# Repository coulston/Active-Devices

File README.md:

Here is a set of resources that I've developed while a faculty member at the Colorado School of Mines.  These resources come in two flavors:

## Laboratories

The labs presented here require students to predict circuit behavior using circuit theory, simulate the circuit, and then build the circuit.  The first two
sets of labs below require multiple lab session to complete, showing students how combine building block circuits to produce complex behavior.
* The design/test/assembly of a BJT curve tracer on a custom PCB.  Based on w2aew's design presented on this [YouTube](https://www.youtube.com/watch?v=ZOLLoa2fH24) video.
* The design/test/assembly of an audio amplifier and audio frequency filters on a custom PCB.
* The analysis of a prebuilt, fully analog, PID controller.
* The analysis of a prebuilt full-bridge Rectifier/Buck converter.

## Workbook
I remember working problems from Schaums outline series as an undergraduate.  Working a long series of similar but distinct circuit
problems helped me hone my skill.  Most textbooks have a small set of problems to work; a volume that did not consistently produce
mastery in my students.  So I spent a summer writing the circuit problems that you will find here.  This is a work in progress and
I would certianly apprecaite any suggestions for problems to add.

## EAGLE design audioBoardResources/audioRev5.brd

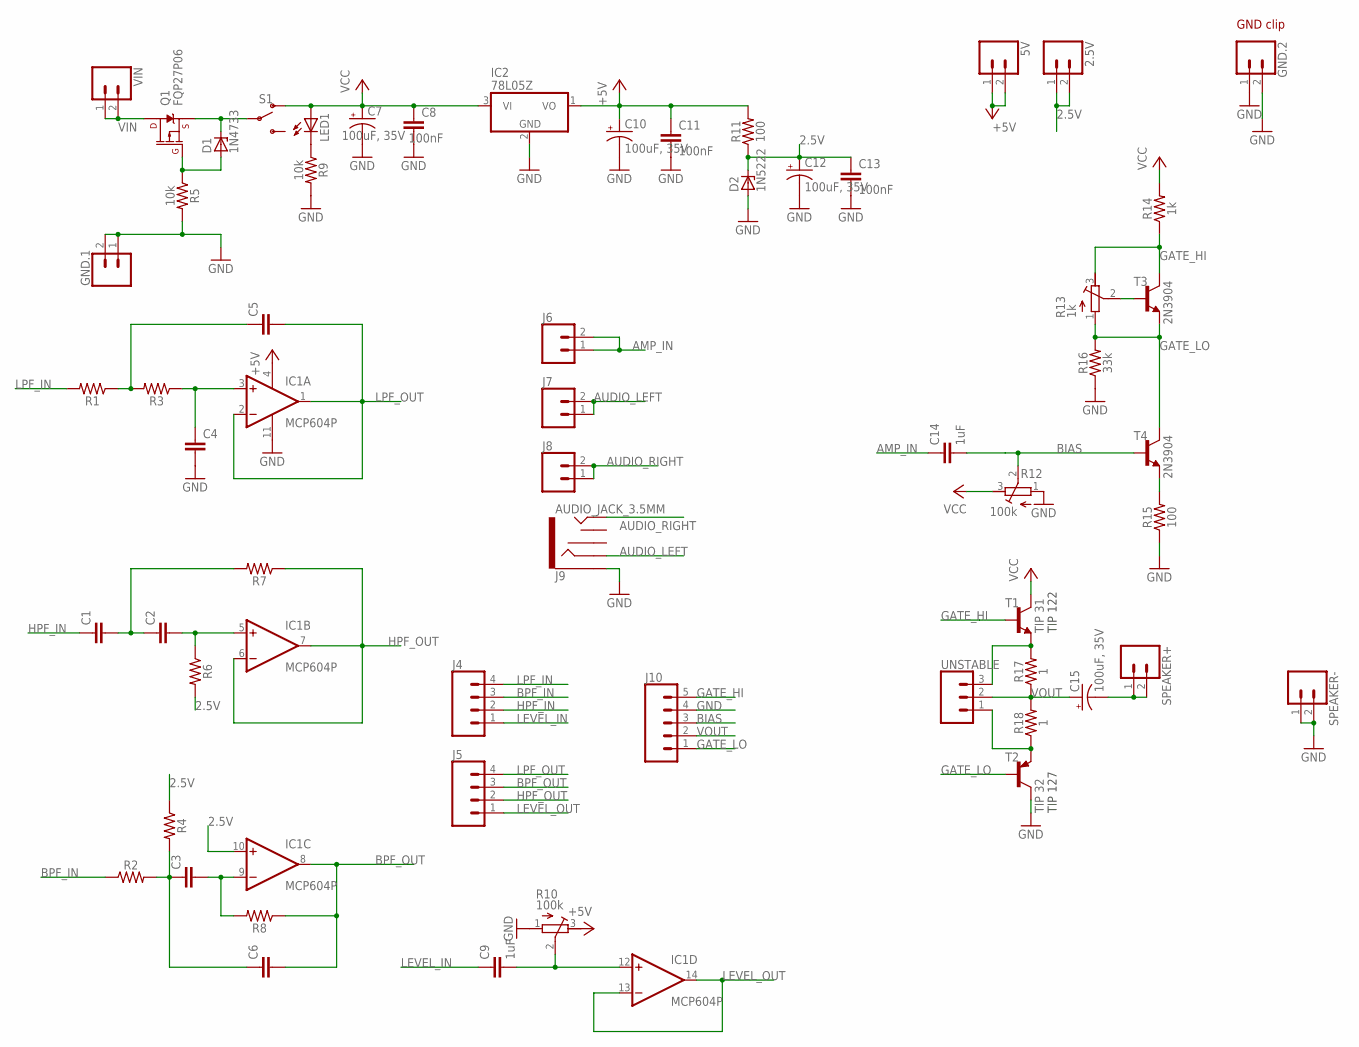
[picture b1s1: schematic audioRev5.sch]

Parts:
2.5V, 5V: CONN_02; 1X02
C1, C2, C3, C4, C5, C6: C-EU025-025X050; C025-025X050
C7, C10, C12, C15: 100uF, 35V; E2,5-6
C8, C11, C13: 100nF; C025-025X050
C9, C14: 1uF; C025-025X050
D1: 1N4733; DO41Z10
D2: 1N5222; DO34Z7
GND.1, GND.2: CONN_02; 1X02
IC1: MCP604P; DIL14
IC2: 78L05Z; TO92
J4, J5: CONN_04LOCK_LONGPADS; 1X04_LOCK_LONGPADS
J6, J7, J8: CONN_02; 1X02
J9: AUDIO_JACK_3.5MM; AUDIO-JACK
J10: CONN_05PTH_LONGPADS; 1X05_LONGPADS
LED1: LED5MM
Q1: FQP27P06; TO220V
R1, R2, R3, R4, R6, R7, R8: RESISTORAXIAL-0.3; AXIAL-0.3
R5, R9: 10k; AXIAL-0.3
R10, R12: 100k; RTRIM3296W
R11, R15: 100; AXIAL-0.3
R13: 1k; RTRIM3296W
R14: 1k; AXIAL-0.3
R16: 33k; AXIAL-0.3
R17, R18: 1; AXIAL-0.3
S1: SWITCH-SPDT-PTH-11.6X4.0MM; SWITCH_SPDT_PTH_11.6X4.0MM
SPEAKER+: CONN_02; 1X02
SPEAKER-: CONN_02; 1X02
T1: TIP 31; TO220V
T2: TIP 32; TO220V
T3, T4: 2N3904; TO92-EBC
UNSTABLE: CONN_03LOCK_LONGPADS; 1X03_LOCK_LONGPADS
VIN: CONN_02; 1X02

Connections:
2.5V: 2.5V.1, 2.5V.2, C12.+, C13.1, D2.C, IC1.10 (+IN), R4.P$1 (1), R6.P$2 (2), R11.P$1 (1)
+5V: 5V.1, 5V.2, C10.+, C11.1, IC1.4 (V+), IC2.1 (VO), R10.3 (E), R11.P$2 (2)
AMP_IN: C14.1, J6.1, J6.2
AUDIO_LEFT: J7.1, J7.2, J9.RING
AUDIO_RIGHT: J8.1, J8.2, J9.TIP
BIAS: C14.2, J10.3, R12.2 (S), T4.B
BPF_IN: J4.3, R2.P$1 (1)
BPF_OUT: C6.2, IC1.8 (OUT), J5.3, R8.P$1 (1)
GATE: D1.A, Q1.1 (G), R5.P$1 (1)
GATE_HI: J10.5, R13.3 (E), R14.P$1 (1), T1.1 (B), T3.C
GATE_LO: J10.1, R13.1 (A), R16.P$2 (2), T2.1 (B), T3.E, T4.C
GND: C4.2, C7.-, C8.2, C10.-, C11.2, C12.-, C13.2, D2.A, GND.1.1, GND.1.2, GND.2.1, GND.2.2, IC1.11 (V-), IC2.2 (GND), J9.SLEEVE, J10.4, R5.P$2 (2), R9.P$2 (2), R10.1 (A), R12.1 (A), R15.P$1 (1), R16.P$1 (1), SPEAKER-.1, SPEAKER-.2, T2.2 (C)
HPF_IN: C1.1, J4.2
HPF_OUT: IC1.6 (-IN), IC1.7 (OUT), J5.2, R7.P$1 (1)
LEVEL_IN: C9.1, J4.1
LEVEL_OUT: IC1.13 (-IN), IC1.14 (OUT), J5.1
LPF_IN: J4.4, R1.P$2 (2)
LPF_OUT: C5.2, IC1.1 (OUT), IC1.2 (-IN), J5.4
unnamed: R18.P$1 (1), T2.3 (E), UNSTABLE.1
unnamed: R17.P$2 (2), T1.3 (E), UNSTABLE.3
unnamed: R15.P$2 (2), T4.E
unnamed: C3.1, C6.1, R2.P$2 (2), R4.P$2 (2)
unnamed: C4.1, IC1.3 (+IN), R3.P$1 (1)
unnamed: C5.1, R1.P$1 (1), R3.P$2 (2)
unnamed: C3.2, IC1.9 (-IN), R8.P$2 (2)
unnamed: C2.2, IC1.5 (+IN), R6.P$1 (1)
unnamed: C1.2, C2.1, R7.P$2 (2)
unnamed: C9.2, IC1.12 (+IN), R10.2 (S)
unnamed: C15.-, SPEAKER+.1, SPEAKER+.2
unnamed: LED1.K (C), R9.P$1 (1)
unnamed: R13.2 (S), T3.B
SOURCE: D1.C, Q1.3 (S), S1.2
VCC: C7.+, C8.1, IC2.3 (VI), LED1.A, R12.3 (E), R14.P$2 (2), S1.1 (O), T1.2 (C)
VIN: Q1.2 (D), VIN.1, VIN.2
VOUT: C15.+, J10.2, R17.P$1 (1), R18.P$2 (2), UNSTABLE.2

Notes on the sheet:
GND clip
TIP 122
TIP 127

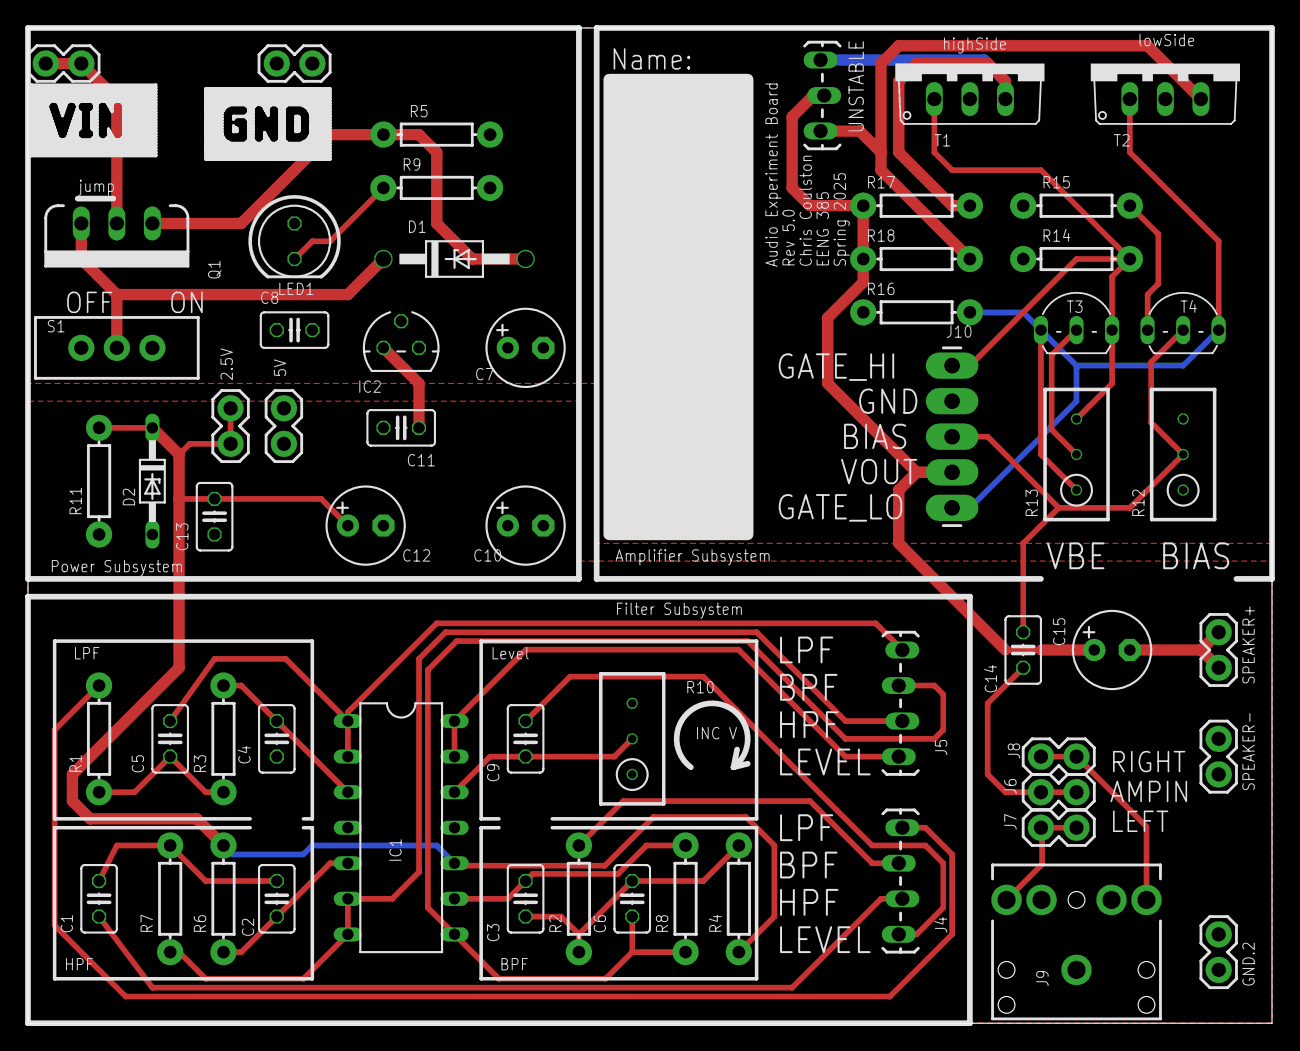
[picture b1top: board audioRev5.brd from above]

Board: 2 copper layers, 88.9 x 71.1 mm, 59 parts (0 on the bottom side), 35 nets.

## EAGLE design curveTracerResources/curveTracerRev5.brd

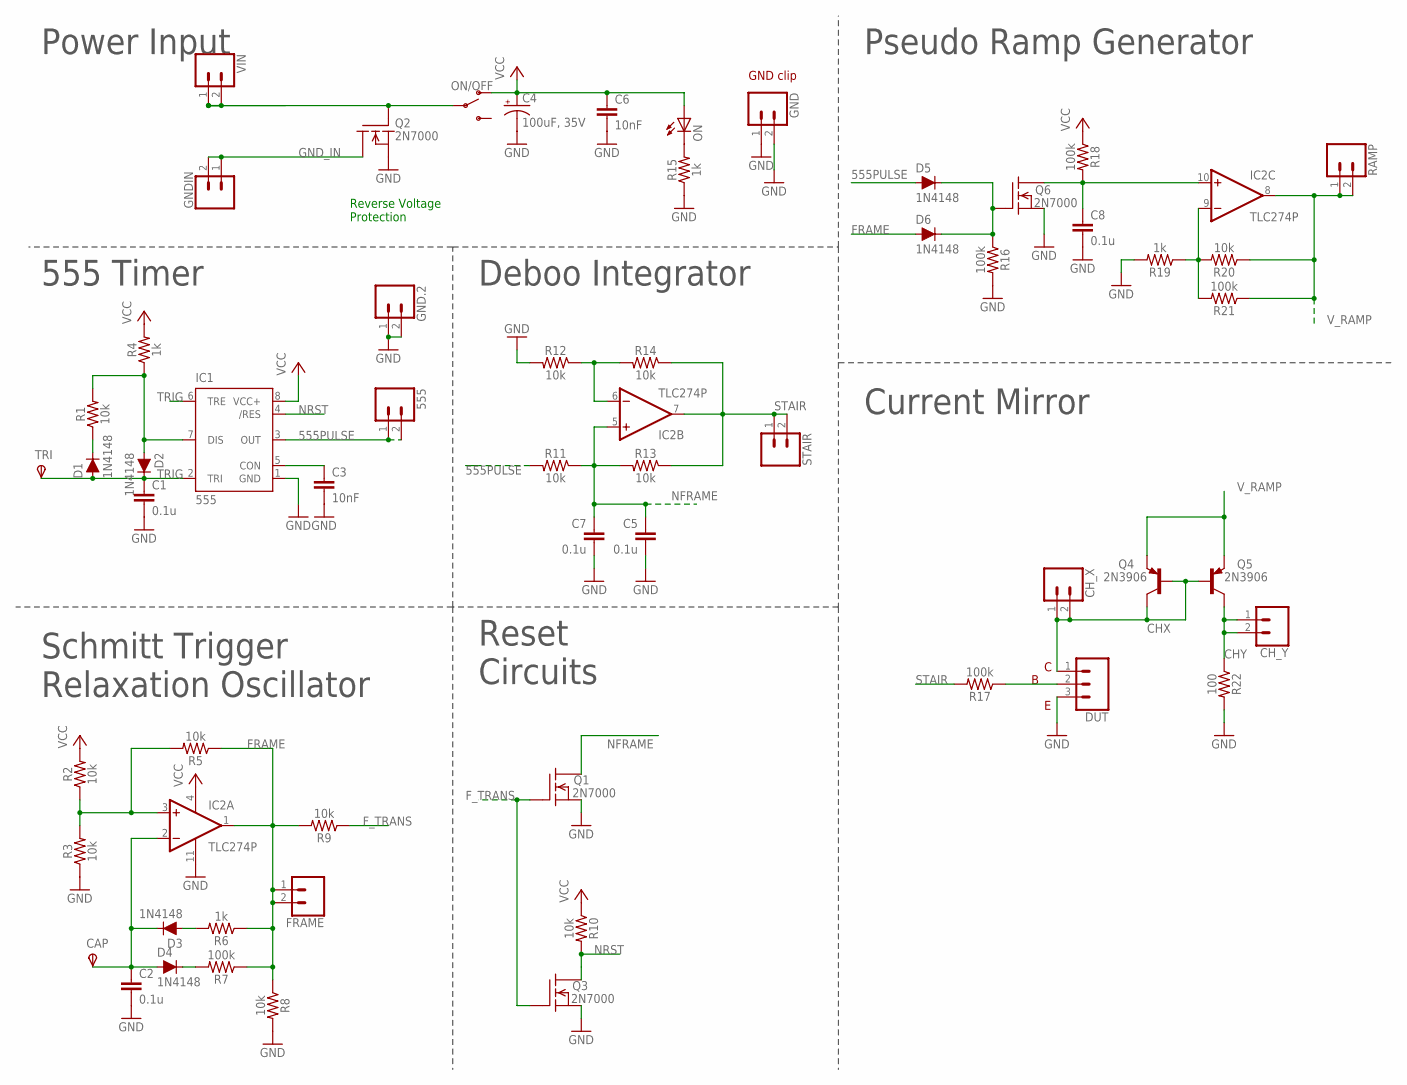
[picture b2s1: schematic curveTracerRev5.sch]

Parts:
555: CONN_02; 1X02
C1, C2, C5, C7, C8: 0.1u; C050-024X044
C3, C6: 10nF; C050-024X044
C4: 100uF, 35V; E2,5-6
CAP: TPSPAD1-13Y; P1-13Y
CH_X: CONN_02; 1X02
CH_Y: CONN_02; 1X02
D1, D2, D3, D4, D5, D6: 1N4148; DIODE-1N4148
DUT: CONN_03LOCK_LONGPADS; 1X03_LOCK_LONGPADS
FRAME: CONN_02; 1X02
GND, GND.2: CONN_02; 1X02
GNDIN: CONN_02; 1X02
IC1: 555; DIP08
IC2: TLC274P; DIL14
ON: LED5MM
ON/OFF: SWITCH-SPDT-PTH-11.6X4.0MM; SWITCH_SPDT_PTH_11.6X4.0MM
Q1, Q2, Q3, Q6: 2N7000; TO-92
Q4, Q5: 2N3906; TO92
R1, R2, R3, R5, R8, R9, R10, R11, R12, R13, R14, R20: 10k; AXIAL-0.3
R4, R6, R15, R19: 1k; AXIAL-0.3
R7, R16, R17, R18, R21: 100k; AXIAL-0.3
R22: 100; AXIAL-0.3
RAMP: CONN_02; 1X02
STAIR: CONN_02; 1X02
TRI: TPSPAD1-13Y; P1-13Y
VIN: CONN_02; 1X02

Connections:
555PULSE: 555.1, 555.2, D5.A, IC1.3 (OUT), R11.P$2 (2)
CHX: CH_X.1, CH_X.2, DUT.1, Q4.1 (C), Q4.2 (B), Q5.2 (B)
CHY: CH_Y.1, CH_Y.2, Q5.1 (C), R22.P$1 (1)
FRAME: D6.A, FRAME.1, FRAME.2, IC2.1 (OUT), R5.P$1 (1), R6.P$1 (1), R7.P$1 (1), R8.P$1 (1), R9.P$2 (2)
F_TRANS: Q1.2 (G), Q3.2 (G), R9.P$1 (1)
GND: C1.2, C2.2, C3.2, C4.-, C5.2, C6.2, C7.2, C8.2, DUT.3, GND.1, GND.2, GND.2.1, GND.2.2, IC1.1 (GND), IC2.11 (V-), Q1.1 (S), Q2.1 (S), Q3.1 (S), Q6.1 (S), R3.P$1 (1), R8.P$2 (2), R12.P$2 (2), R15.P$1 (1), R16.P$2 (2), R19.P$2 (2), R22.P$2 (2)
GND_IN: GNDIN.1, GNDIN.2, Q2.3 (D)
unnamed: ON/OFF.2, Q2.2 (G), VIN.1, VIN.2
unnamed: ON.K (C), R15.P$2 (2)
unnamed: D1.C, R1.P$1 (1)
unnamed: D2.A, IC1.7 (DIS), R1.P$2 (2), R4.P$1 (1)
unnamed: D3.A, R6.P$2 (2)
unnamed: C3.1, IC1.5 (CON)
unnamed: C2.1, CAP.TP, D3.C, D4.A, IC2.2 (-IN)
unnamed: IC2.3 (+IN), R2.P$1 (1), R3.P$2 (2), R5.P$2 (2)
unnamed: D4.C, R7.P$2 (2)
unnamed: D5.C, D6.C, Q6.2 (G), R16.P$1 (1)
unnamed: DUT.2, R17.P$1 (1)
unnamed: IC2.6 (-IN), R12.P$1 (1), R14.P$2 (2)
unnamed: IC2.9 (-IN), R19.P$1 (1), R20.P$2 (2), R21.P$2 (2)
unnamed: C8.1, IC2.10 (+IN), Q6.3 (D), R18.P$2 (2)
NFRAME: C5.1, C7.1, IC2.5 (+IN), Q1.3 (D), R11.P$1 (1), R13.P$2 (2)
NRST: IC1.4 (/RES), Q3.3 (D), R10.P$2 (2)
STAIR: IC2.7 (OUT), R13.P$1 (1), R14.P$1 (1), R17.P$2 (2), STAIR.1, STAIR.2
TRIG: C1.1, D1.A, D2.C, IC1.2 (TRI), IC1.6 (TRE), TRI.TP
VCC: C4.+, C6.1, IC1.8 (VCC+), IC2.4 (V+), ON.A, ON/OFF.1 (O), R2.P$2 (2), R4.P$2 (2), R10.P$1 (1), R18.P$1 (1)
V_RAMP: IC2.8 (OUT), Q4.3 (E), Q5.3 (E), R20.P$1 (1), R21.P$1 (1), RAMP.1, RAMP.2

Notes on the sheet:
GND clip
Power Input
555 Timer
Schmitt Trigger Relaxation Oscillator
Deboo Integrator
Reset Circuits
Pseudo Ramp Generator
Current Mirror
Reverse Voltage Protection

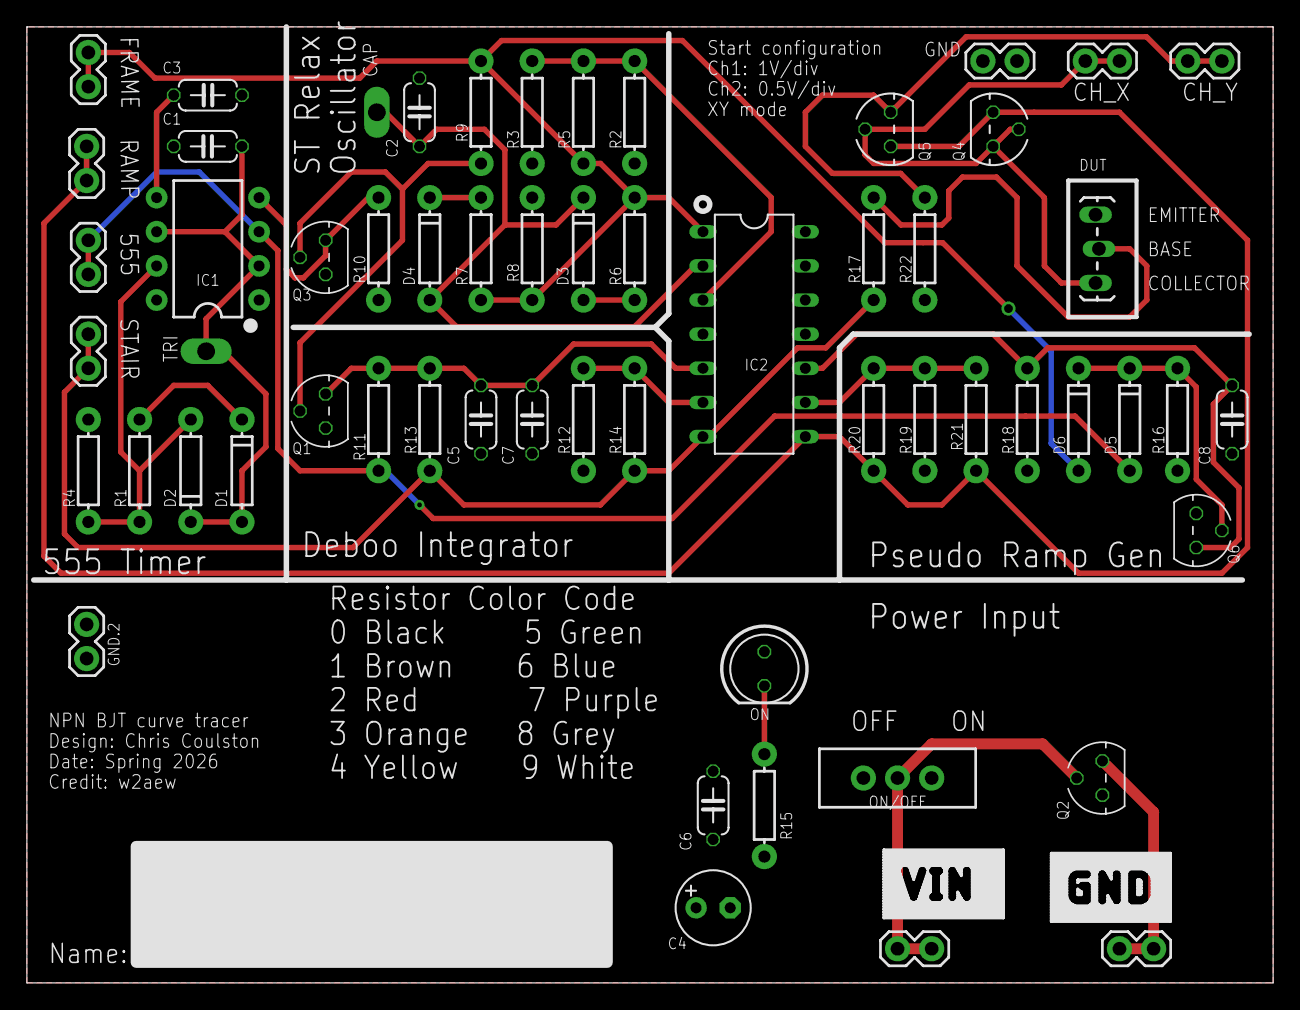
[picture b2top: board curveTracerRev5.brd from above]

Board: 2 copper layers, 92.7 x 71.1 mm, 59 parts (0 on the bottom side), 27 nets.

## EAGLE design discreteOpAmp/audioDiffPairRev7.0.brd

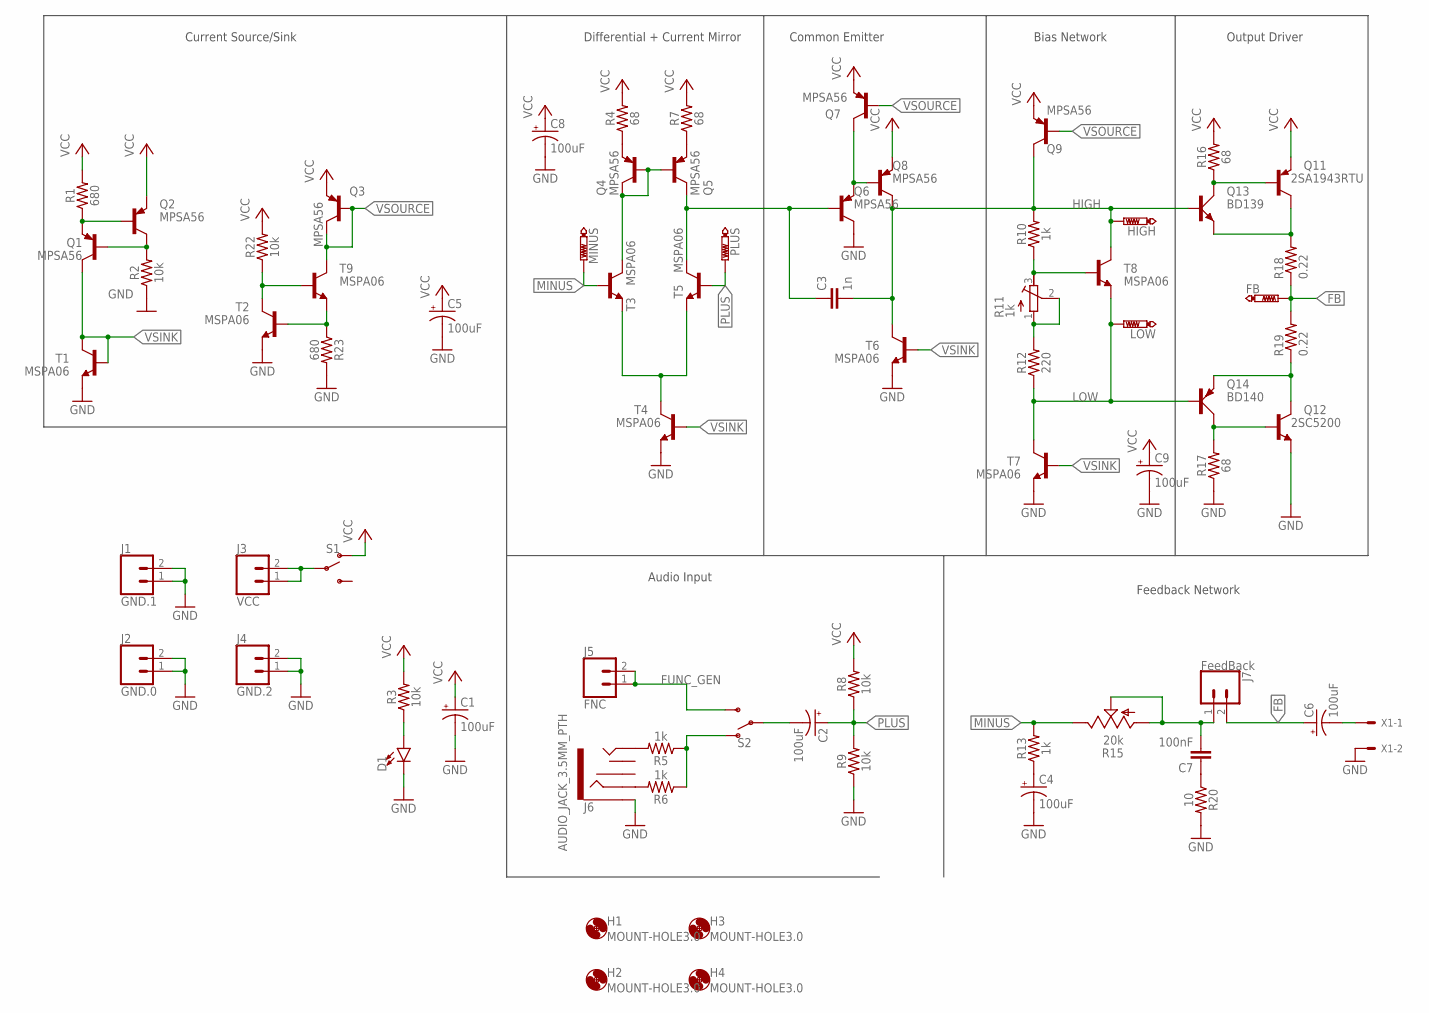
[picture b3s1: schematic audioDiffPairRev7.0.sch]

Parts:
C1, C2, C4, C5, C6, C8, C9: 100uF; CPOL-RADIAL-2.5MM-6.5MM
C3: 1n; C025-025X050
C7: 100nF; C025-025X050
D1: LED5MM; LED_5MM
FB: PTR1PAD1-13Y; P1-13Y
H1, H2, H3, H4: MOUNT-HOLE3.0; 3,0
HIGH: PTR1PAD1-13Y; P1-13Y
J1: GND.1; 1X02_LOCK_LONGPADS
J2: GND.0; 1X02_LOCK_LONGPADS
J3: VCC; 1X02_LOCK_LONGPADS
J4: GND.2; 1X02_LOCK_LONGPADS
J5: FNC; 1X02_LOCK_LONGPADS
J6: AUDIO_JACK_3.5MM_PTH; AUDIO-JACK
J7: FeedBack; 1X02_LOCK_LONGPADS
LOW: PTR1PAD1-13Y; P1-13Y
MINUS: PTR1PAD1-13Y; P1-13Y
PLUS: PTR1PAD1-13Y; P1-13Y
Q1, Q2, Q3, Q4, Q5, Q6, Q7, Q8, Q9: MPSA56; TO92-CBE
Q11: 2SA1943RTU; TO545P2000X500X2900-3
Q12: 2SC5200; TO545P2020X520X2910-3
Q13: BD139; TO126AV
Q14: BD140; TO126AV
R1, R23: 680; AXIAL-0.3
R2, R3, R8, R9, R22: 10k; AXIAL-0.3
R4, R7, R16, R17: 68; AXIAL-0.3
R5, R6, R10, R13: 1k; AXIAL-0.3
R11: 1k; RTRIM3296W
R12: 220; AXIAL-0.3
R15: 20k; EVUF
R18, R19: 0.22; 0411/15
R20: 10; AXIAL-0.3
S1, S2: SWITCH-SPDT-PTH-11.6X4.0MM-LOCK; SWITCH_SPDT_PTH_11.6X4.0MM_LOCK
T1, T2, T3, T4, T5, T6, T7, T8, T9: MSPA06; TO92-EBC
X1: KK-156-2

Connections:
FB: C6.1 (+), FB.TP, J7.2, R18.1, R19.2
FUNC_GEN: J5.1, J5.2, S2.3 (S)
GND: C1.2 (-), C4.2 (-), C5.2 (-), C8.2 (-), C9.2 (-), D1.K (C), J1.1, J1.2, J2.1, J2.2, J4.1, J4.2, J6.SLEEVE, Q6.C, Q12.3 (E), R2.P$1 (1), R9.P$1 (1), R17.P$1 (1), R20.P$2 (2), R23.P$2 (2), T1.E, T2.E, T4.E, T6.E, T7.E, X1.2
HIGH: C3.2, HIGH.TP, Q8.C, Q9.C, Q13.B, R10.P$2 (2), T6.C, T8.C
HIGH1: Q6.E, Q7.C, Q8.B
LOW: LOW.TP, Q14.B, R12.P$1 (1), T7.C, T8.E
MINUS: MINUS.TP, R13.P$2 (2), R15.3 (E), T3.B
unnamed: Q1.E, Q2.B, R1.P$1 (1)
unnamed: Q1.B, Q2.C, R2.P$2 (2)
unnamed: Q4.B, Q4.C, Q5.B, T3.C
unnamed: C3.1, Q5.C, Q6.B, T5.C
unnamed: C7.1, R20.P$1 (1)
unnamed: C7.2, J7.1, R15.1 (A), R15.2 (S)
unnamed: Q4.E, R4.P$1 (1)
unnamed: Q5.E, R7.P$1 (1)
unnamed: D1.A, R3.P$1 (1)
unnamed: Q11.1 (B), Q13.C, R16.P$1 (1)
unnamed: J3.1, J3.2, S1.2
unnamed: J6.RING, R6.P$2 (2)
unnamed: R22.P$1 (1), T2.C, T9.B
unnamed: C2.2 (-), S2.2
unnamed: T3.E, T4.C, T5.E
unnamed: Q12.1 (B), Q14.C, R17.P$2 (2)
unnamed: Q12.2 (C), Q14.E, R19.1
unnamed: C4.1 (+), R13.P$1 (1)
unnamed: R23.P$1 (1), T2.B, T9.E
unnamed: J6.TIP, R5.P$2 (2)
unnamed: R5.P$1 (1), R6.P$1 (1), S2.1 (O)
unnamed: C6.2 (-), X1.1
unnamed: Q11.2 (C), Q13.E, R18.2
unnamed: R10.P$1 (1), R11.3 (E), T8.B
unnamed: R11.1 (A), R11.2 (S), R12.P$2 (2)
PLUS: C2.1 (+), PLUS.TP, R8.P$1 (1), R9.P$2 (2), T5.B
VCC: C1.1 (+), C5.1 (+), C8.1 (+), C9.1 (+), Q2.E, Q3.E, Q7.E, Q8.E, Q9.E, Q11.3 (E), R1.P$2 (2), R3.P$2 (2), R4.P$2 (2), R7.P$2 (2), R8.P$2 (2), R16.P$2 (2), R22.P$2 (2), S1.1 (O)
VSINK: Q1.C, T1.B, T1.C, T4.B, T6.B, T7.B
VSOURCE: Q3.B, Q3.C, Q7.B, Q9.B, T9.C

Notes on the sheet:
Common Emitter
Differential + Current Mirror
Current Source/Sink
Audio Input
Feedback Network
Bias Network
Output Driver

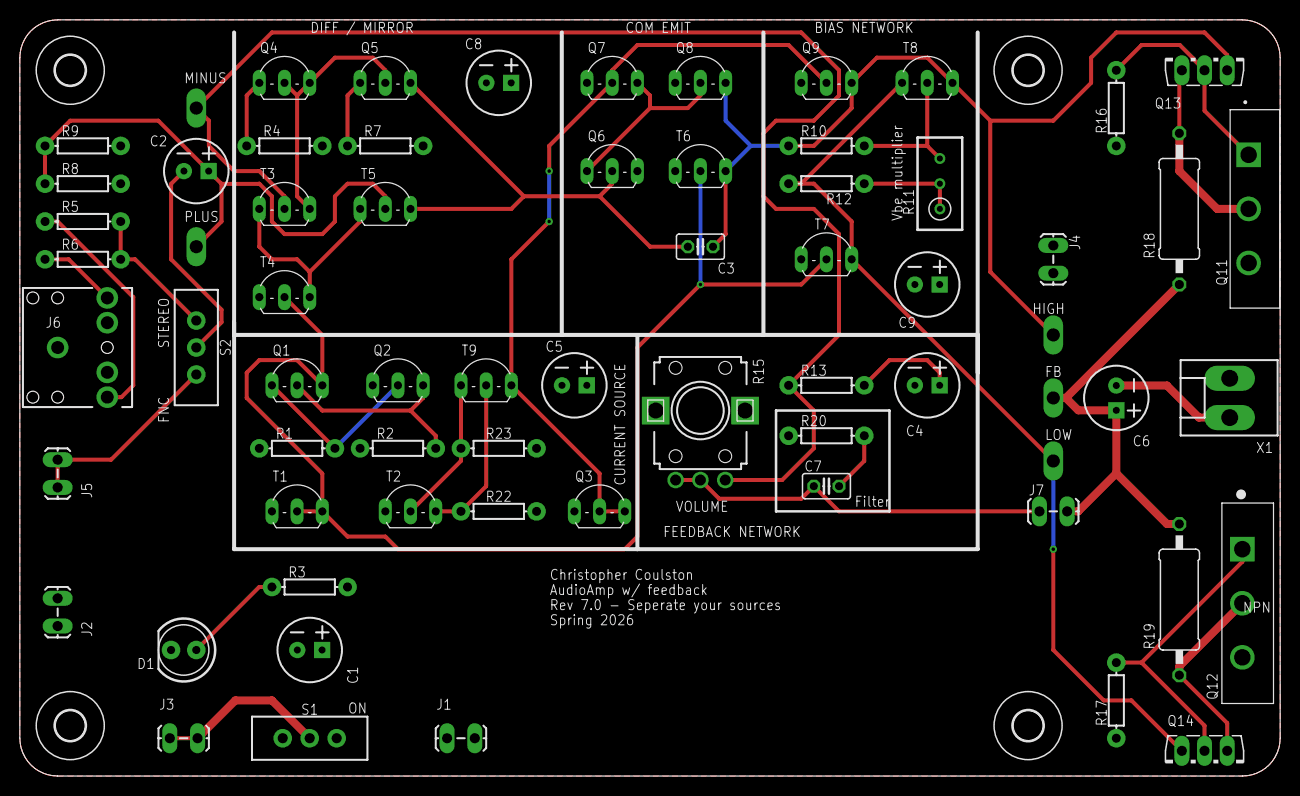
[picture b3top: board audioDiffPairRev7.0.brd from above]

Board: 2 copper layers, 127.0 x 76.2 mm, 72 parts (0 on the bottom side), 36 nets.

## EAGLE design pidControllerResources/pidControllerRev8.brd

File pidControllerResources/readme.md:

# PID Controller

<image of PID Controller>

The PID Controller board is designed as a practical laboratory experience for students to understand how to characterize a plant, and tune a PID Controller.  Through this process you will achieve the following learning objectives:
* Analyze an opamp circuit that implements a PID controller and plant.
* Characterize a plant
  * Determine the transfer function of the plant
  * Determine the frequency reponse of the plant by building its Bode plot
  * Compute gain and phase margin of a plant by building its Nyquist plot
* Hands on tuning of a PID controller.

# Documentation
* [PID Laboratory](../Labs/lab50%20pidController/pidControllerLab.pdf)
* Videos
    * Overview
    * Characterizing the plant
* Hardware
    * PID Controller [Schematic](./pidControllerRev8schematic.pdf) and [Layout](./pidControllerRev8layout.pdf)
    * Source files to build your own
       * EAGLE CAD [Schematic](./manufacture/pidControllerRev8.sch) and [Layout](./manufacture/pidControllerRev8.brd)
       * [Gerber Files](./manufacture/pidControlRev8Gerber)
       * [Bill of Materials](./manufacture/pidControllerMaster_BOM.xlsx)
       * [Centroid File](./manufacture/pidController_Centroid.xlsx)

# Respository Contents

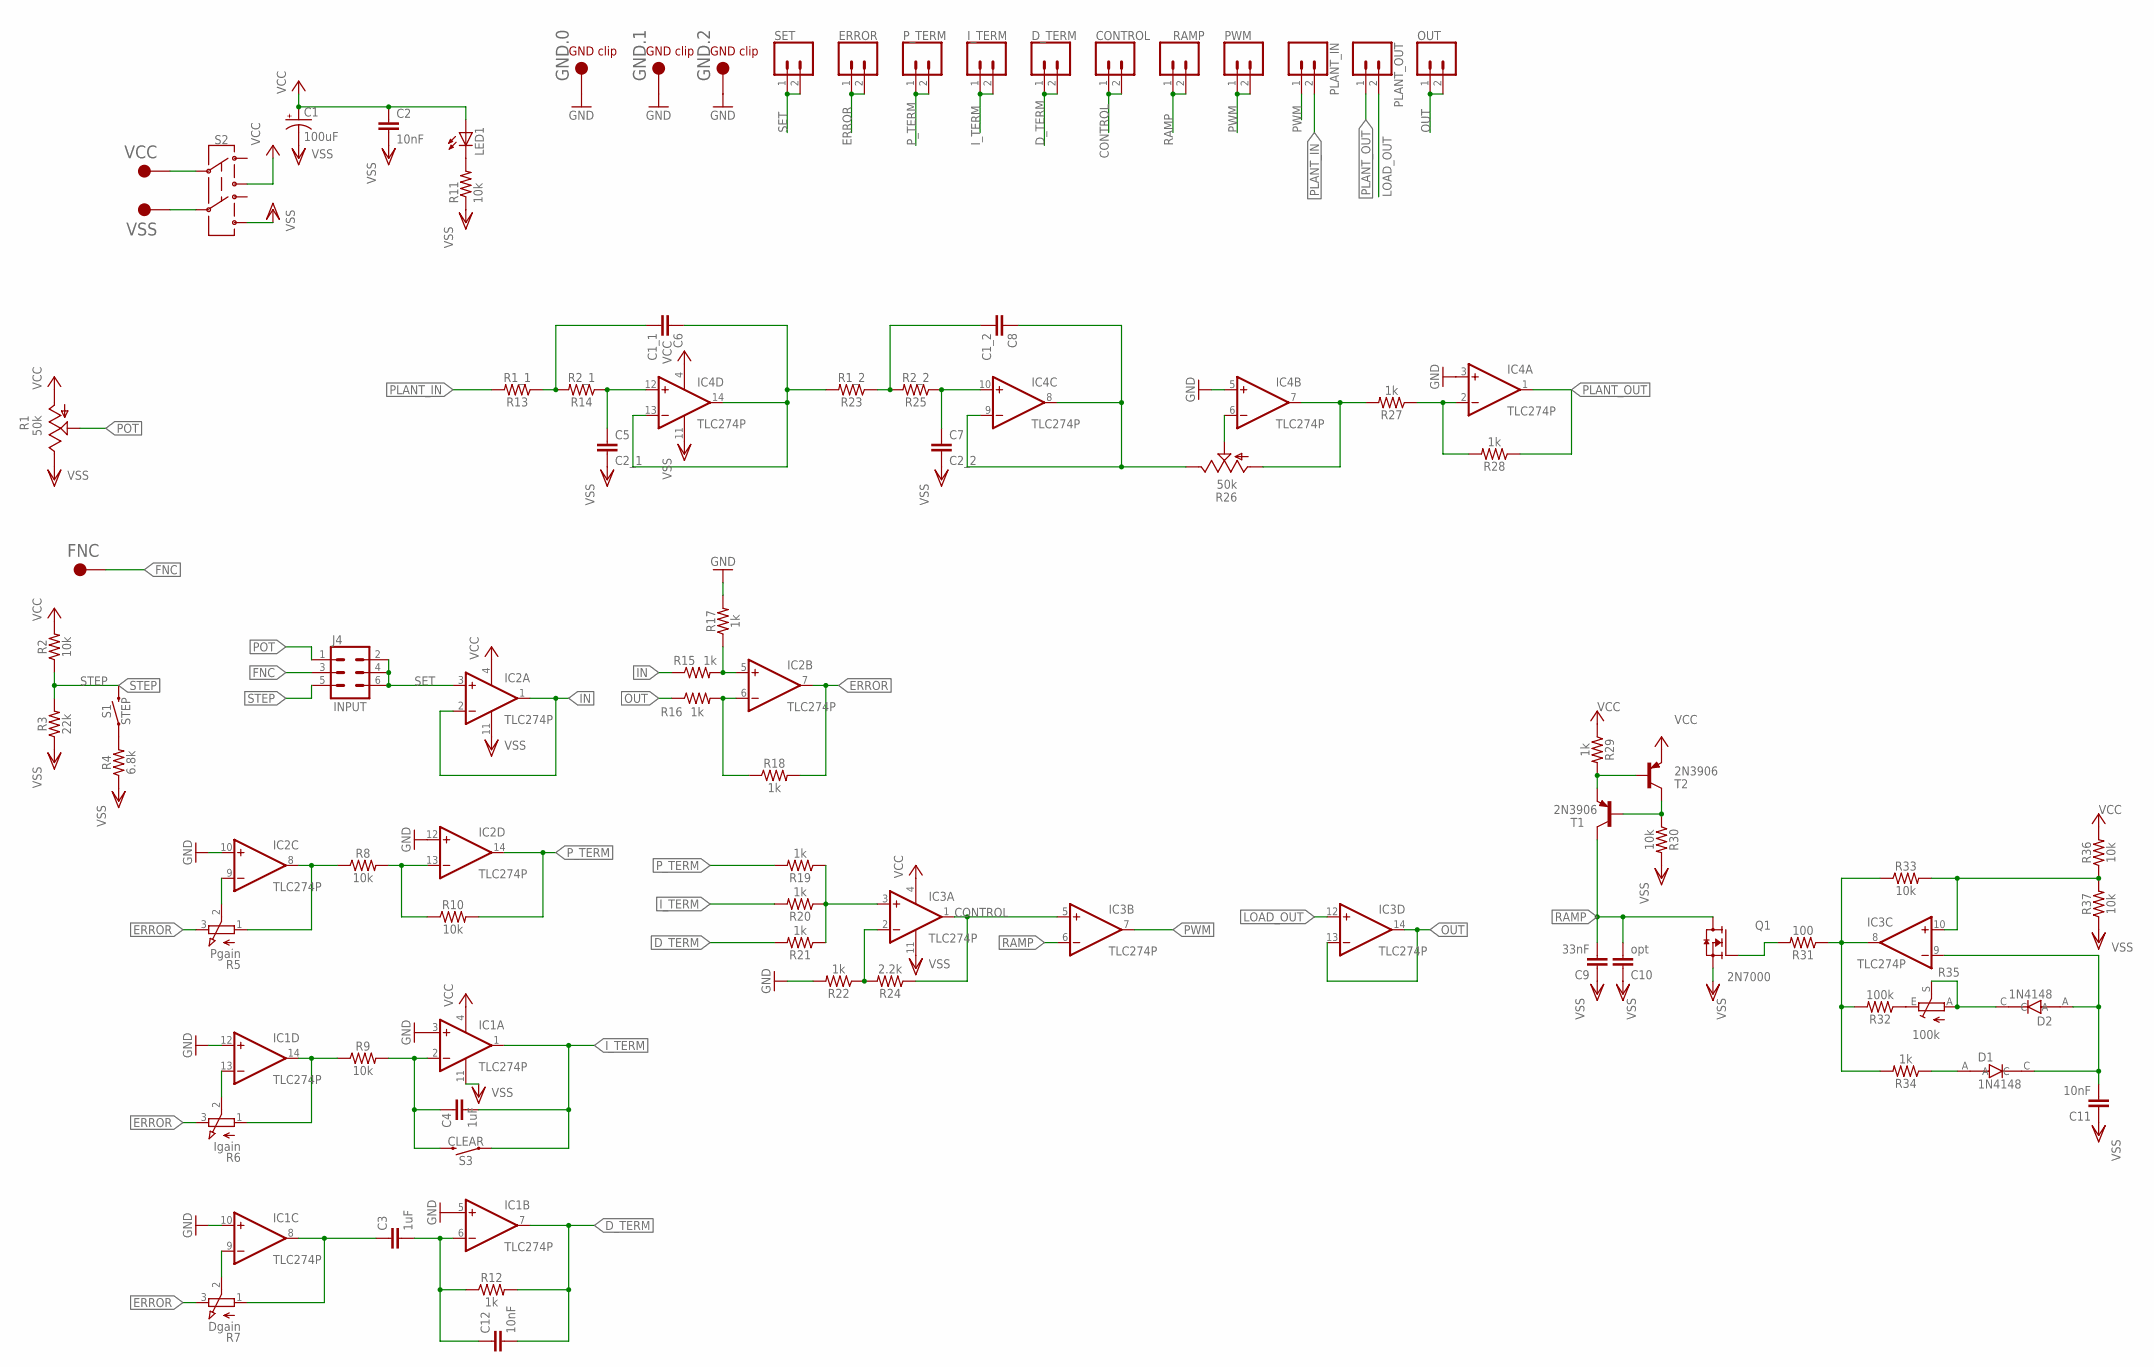
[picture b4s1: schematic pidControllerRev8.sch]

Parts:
C1: 100uF; SANYO-OSCON_C
C2, C11, C12: 10nF; C1206
C3, C4: 1uF; C1206
C5: C2_1; C1206
C6: C1_1; C1206
C7: C2_2; C1206
C8: C1_2; C1206
C9: 33nF; C1206
C10: opt; C050-024X044
CONTROL: CONN_02LOCK; 1X02_LOCK
D1, D2: 1N4148; SOD2513X120N
D_TERM: CONN_02LOCK; 1X02_LOCK
ERROR: CONN_02LOCK; 1X02_LOCK
FNC: 5016; KEYSTONE_5016
GND.0, GND.1, GND.2: 5016; KEYSTONE_5016
IC1, IC2, IC3, IC4: TLC274P; DIL14
I_TERM: CONN_02LOCK; 1X02_LOCK
J4: INPUT; 2X3
LED1: LEDCHIPLED_1206; CHIPLED_1206
OUT: CONN_02LOCK; 1X02_LOCK
PLANT_IN: CONN_02LOCK; 1X02_LOCK
PLANT_OUT: CONN_02LOCK; 1X02_LOCK
PWM: CONN_02LOCK; 1X02_LOCK
P_TERM: CONN_02LOCK; 1X02_LOCK
Q1: 2N7000; TO92254P458H750-3
R1, R26: 50k; B25P
R2, R8, R9, R10, R30, R33, R36, R37: 10k; 1206
R3: 22k; 1206
R4: 6.8k; 1206
R5: Pgain; EVUF
R6: Igain; EVUF
R7: Dgain; EVUF
R11: 10k; R1206
R12, R15, R16, R17, R18, R19, R20, R21, R22, R27, R28, R29, R34: 1k; 1206
R13: R1_1; 1206
R14: R2_1; 1206
R23: R1_2; 1206
R24: 2.2k; 1206
R25: R2_2; 1206
R31: 100; 1206
R32: 100k; 1206
R35: 100k; S64W
RAMP: CONN_02LOCK; 1X02_LOCK
S1: STEP; TACTILE_SWITCH_SMD_5.2MM
S2: SWITCH-DPDT-SMD-AYZ0202; SWITCH_DPDT_SMD_AYZ0202
S3: CLEAR; TACTILE_SWITCH_SMD_5.2MM
SET: CONN_02LOCK; 1X02_LOCK
T1, T2: 2N3906; TO92-EBC
VCC: 5016; KEYSTONE_5016
VSS: 5016; KEYSTONE_5016

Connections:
CONTROL: CONTROL.1, CONTROL.2, IC3.1 (OUT), IC3.5 (+IN), R24.1
D_TERM: C12.2, D_TERM.1, D_TERM.2, IC1.7 (OUT), R12.2, R21.2
ERROR: ERROR.1, ERROR.2, IC2.7 (OUT), R5.3 (E), R6.3 (E), R7.3 (E), R18.2
FNC: FNC.TP, J4.3
GND: GND.0.TP, GND.1.TP, GND.2.TP, IC1.3 (+IN), IC1.5 (+IN), IC1.10 (+IN), IC1.12 (+IN), IC2.10 (+IN), IC2.12 (+IN), IC4.3 (+IN), IC4.5 (+IN), R17.2, R22.2
IN: IC2.1 (OUT), IC2.2 (-IN), R15.1
I_TERM: C4.2, IC1.1 (OUT), I_TERM.1, I_TERM.2, R20.2, S3.1
LOAD_OUT: IC3.12 (+IN), PLANT_OUT.2
unnamed: IC2.5 (+IN), R15.2, R17.1
unnamed: IC2.6 (-IN), R16.2, R18.1
unnamed: IC4.7 (OUT), R26.A, R27.2
unnamed: C4.1, IC1.2 (-IN), R9.2, S3.3 (2)
unnamed: IC2.8 (OUT), R5.1 (A), R8.1
unnamed: IC3.3 (+IN), R19.1, R20.1, R21.1
unnamed: IC3.2 (-IN), R22.1, R24.2
unnamed: S2.5, VSS.TP
unnamed: IC3.10 (+IN), R33.2, R36.1, R37.2
unnamed: IC4.2 (-IN), R27.1, R28.2
unnamed: IC3.8 (OUT), R31.1, R32.2, R33.1, R34.2
unnamed: R29.2, T1.E, T2.B
unnamed: R30.1, T1.B, T2.C
unnamed: IC1.14 (OUT), R6.1 (A), R9.1
unnamed: S2.2, VCC.TP
unnamed: LED1.C, R11.2
unnamed: C3.1, IC1.8 (OUT), R7.1 (A)
unnamed: IC1.13 (-IN), R6.2 (S)
unnamed: IC2.13 (-IN), R8.2, R10.1
unnamed: R32.1, R35.E
unnamed: IC1.9 (-IN), R7.2 (S)
unnamed: C3.2, C12.1, IC1.6 (-IN), R12.1
unnamed: IC2.9 (-IN), R5.2 (S)
unnamed: R4.2, S1.1
unnamed: C6.2, R13.1, R14.2
unnamed: C5.1, IC4.12 (+IN), R14.1
unnamed: C6.1, IC4.13 (-IN), IC4.14 (OUT), R23.2
unnamed: D1.A, R34.1
unnamed: C8.2, R23.1, R25.2
unnamed: C7.1, IC4.10 (+IN), R25.1
unnamed: C8.1, IC4.8 (OUT), IC4.9 (-IN), R26.E
unnamed: C11.2, D1.C, D2.A, IC3.9 (-IN)
unnamed: IC4.6 (-IN), R26.S
unnamed: Q1.2 (G), R31.2
unnamed: D2.C, R35.A, R35.S
OUT: IC3.13 (-IN), IC3.14 (OUT), OUT.1, OUT.2, R16.1
PLANT_IN: PLANT_IN.2, R13.2
PLANT_OUT: IC4.1 (OUT), PLANT_OUT.1, R28.1
POT: J4.1, R1.S
PWM: IC3.7 (OUT), PLANT_IN.1, PWM.1, PWM.2
P_TERM: IC2.14 (OUT), P_TERM.1, P_TERM.2, R10.2, R19.2
RAMP: C9.2, C10.2, IC3.6 (-IN), Q1.3 (D), RAMP.1, RAMP.2, T1.C
SET: IC2.3 (+IN), J4.2, J4.4, J4.6, SET.1, SET.2
STEP: J4.5, R2.1, R3.2, S1.3 (2)
VCC: C1.+, C2.1, IC1.4 (V+), IC2.4 (V+), IC3.4 (V+), IC4.4 (V+), LED1.A, R1.A, R2.2, R29.1, R36.2, S2.3, T2.E
VSS: C1.-, C2.2, C5.2, C7.2, C9.1, C10.1, C11.1, IC1.11 (V-), IC2.11 (V-), IC3.11 (V-), IC4.11 (V-), Q1.1 (S), R1.E, R3.1, R4.1, R11.1, R30.2, R37.1, S2.6

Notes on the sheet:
GND clip

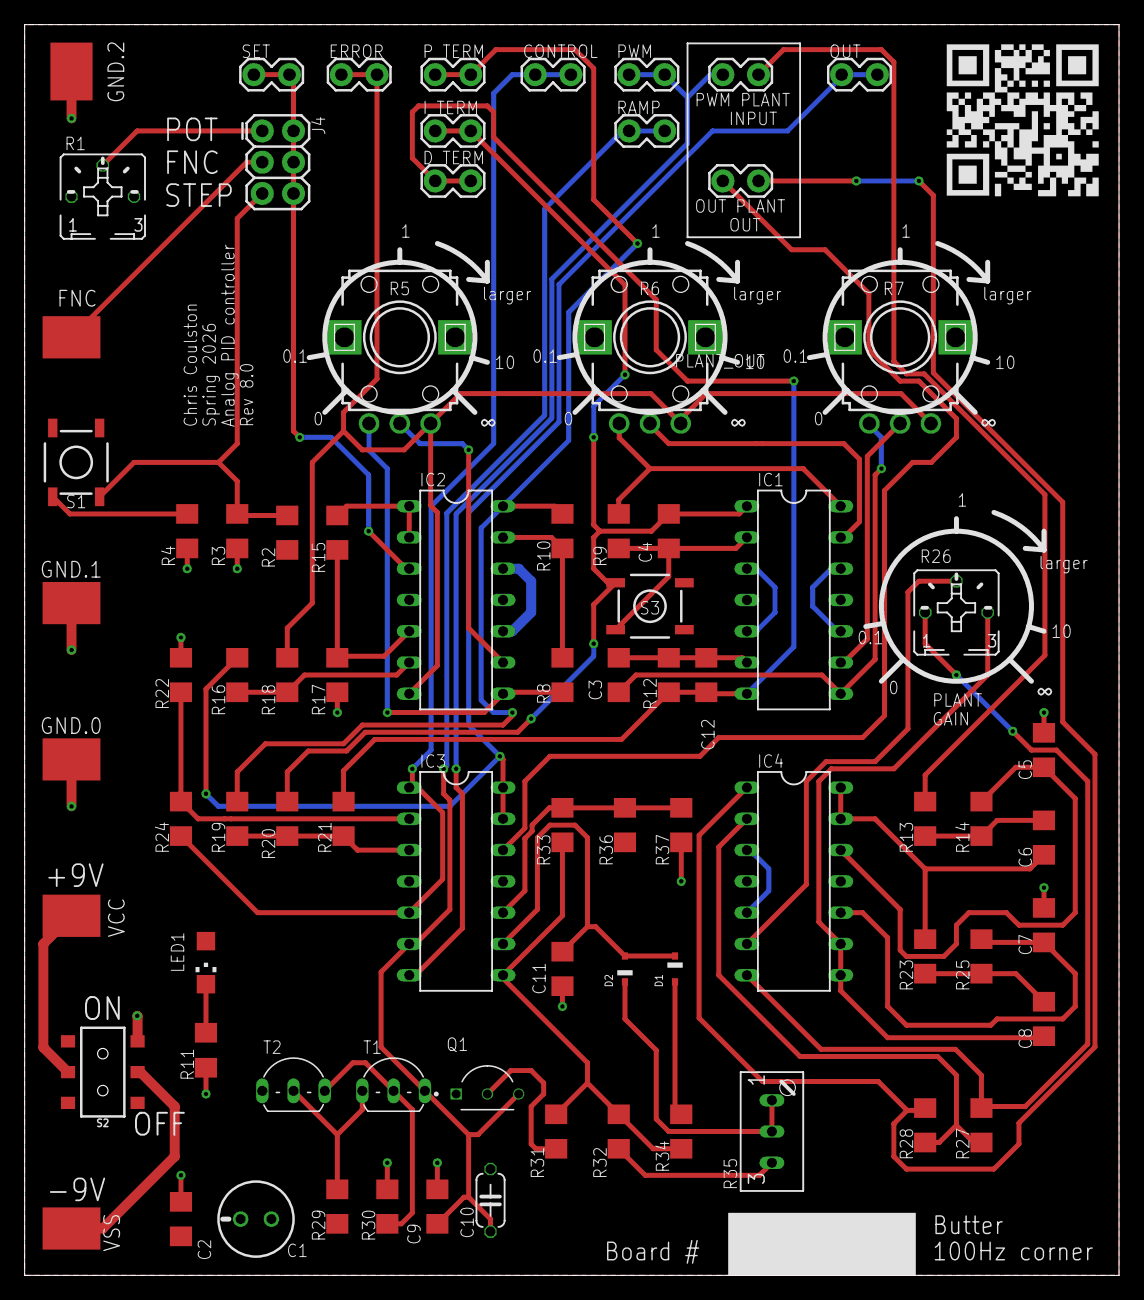
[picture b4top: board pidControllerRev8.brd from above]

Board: 2 copper layers, 88.9 x 101.6 mm, 80 parts (0 on the bottom side), 54 nets.

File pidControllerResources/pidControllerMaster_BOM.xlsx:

Comment | Designator | Footprint | Butter | Bessel | Cheby -3dB
100uF, 35V | C1 | SANYO-OSCON_C | C47891
CAP CER 10nF 50V X7R 1206 | C2, C11, C12 | C1206 | C1846
CAP CER 1uF 50V X7R 1206 | C3, C4 | C1206 | C90539
CAP CER 33nF 50V X7R 1206 | C9 | C1206 | C1864
1N4148 | D1, D2 | SOD-323 | C60580
14P DIP 7.62mm 2.54mm DIP-14 IC Sockets RoHS | IC1, IC2, IC3, IC4 | DIL14 | C2325
CONN HEADER 6POS 2.54mm DUAL ROW TH | J4 | 2X3 | C492420
CONN HEADER 2POS 2.54mm SINGLE ROW TH | PLANT_IN, PLANT_OUT | 1x2 | C492401
LED EMERALD GREEN WATER CLEAR 1206 SMD | LED1 | D1206 | C965825
2N7000 | Q1 | TO-92-2.54mm | C107290
POT 50kΩ 500mW Through Hole | R1, R26 | Through Hole-3P,7x6.8mm | C48997904
RES 1kΩ ±1% 250mW 1206 | R12, R15, R16, R17, R18, R19, R20, R21, R22, R27, R28, R29, R34 | R1206 | C4410
15k | R1_1 | R1206 | C25828 | C17902 | C25834
22k | R2_1 | R1206 | C25830 | C25828 | C17900
100nF | C1_1 | C1206 | C110253 | C110253 | C110253
68nF | C2_1 | C1206 | C1880 | C1880 | C1856
22k | R1_2 | R1206 | C25830 | C17902 | C17916
100k | R2_2 | R1206 | C17900 | C25836 | C17929
100nF | C1_2 | C1206 | C110253 | C110253 | C110253
10nF | C2_2 | C1206 | C1846 | C1864 | C1881
RES 10kΩ ±1% 250mW 1206 | R2, R8, R9, R10, R11, R30, R33, R36, R37 | R1206 | C17902
RES 3.3kΩ ±1% 250mW 1206 | R24 | R1206 | C26032
RES 22kΩ ±1% 250mW 1206 | R3 | R1206 | C25830
RES 100Ω ±1% 250mW 1206 | R31 | R1206 | C17901
RES 100kΩ ±1% 250mW 1206 | R32 | R1206 | C17900
POT 100kΩ Through Hole-3P,9.5x4.9mm Slide Potentiometers RoHS | R35 | Through Hole-3P,9.5x4.9mm | C48997936
RES 6.8kΩ ±1% 250mW 1206 | R4 | R1206 | C26034
POT 10kΩ Through Hole | R5, R6, R7 | EVUF | C209779
SMD-4P,6x6mm Tactile Switches RoHS | S1 | SMD-4P,5.1x5.1mm | C318884
SWITCH SLIDE DPDT SMD | S2 | AYZ0202 | C2906280
2N3906 | T1, T2 | TO-92-3 | C124483
Aligator Connector | FNC,GND.0,GND.1,GND.2,VCC,VSS | Custom | C238129

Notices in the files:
parts and their libraries:
SparkFun-Resistors: Licensing: Creative Commons ShareAlike 4.0 International - https://creativecommons.org/licenses/by-sa/4.0
